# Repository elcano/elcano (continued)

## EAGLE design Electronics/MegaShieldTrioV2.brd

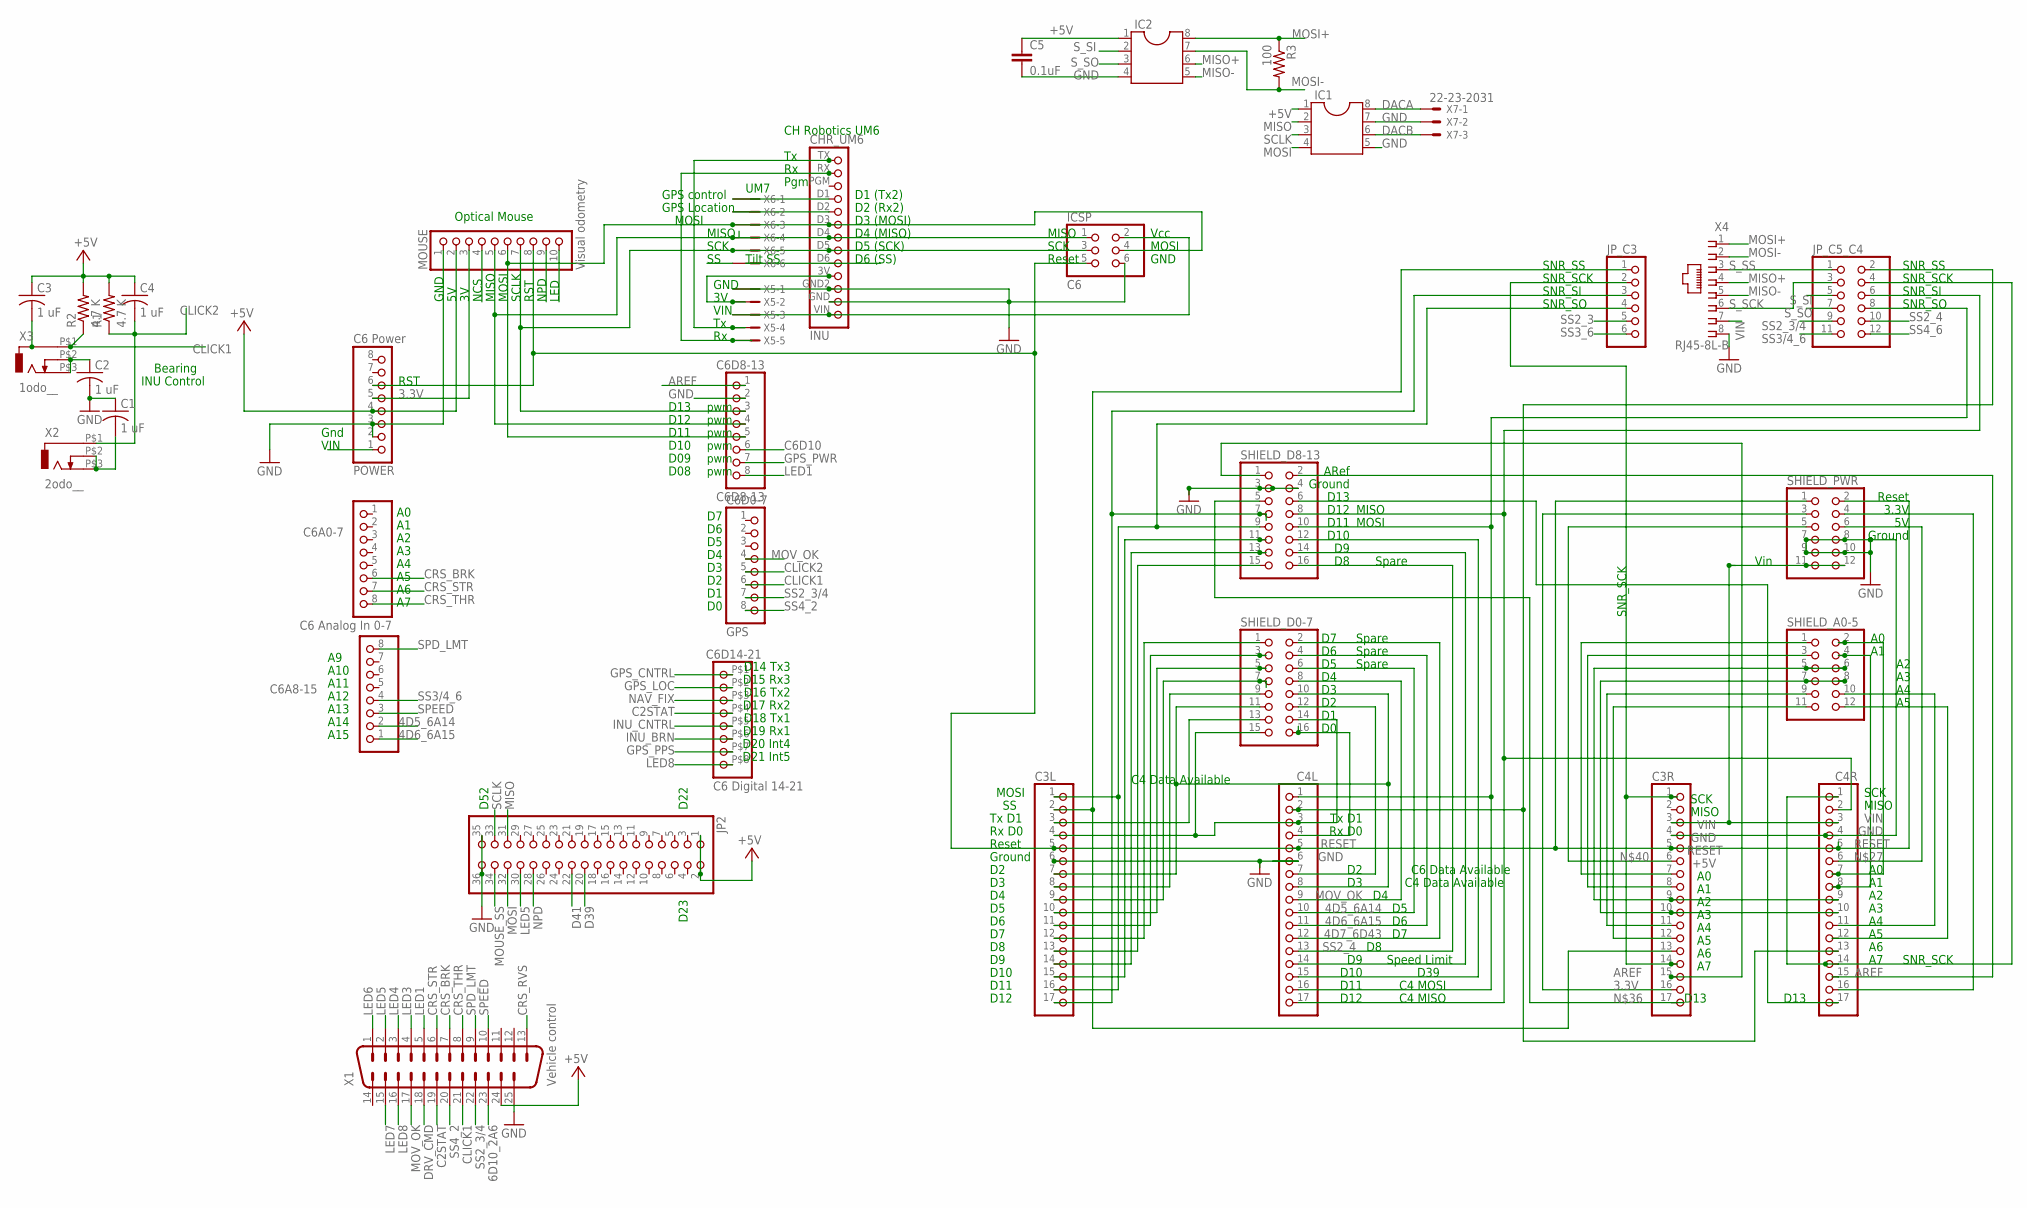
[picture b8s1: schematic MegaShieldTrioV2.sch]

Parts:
C1, C2, C3, C4: 1 uF; C025-030X050
C3L, C3R, C4L, C4R: PINHD-1X17; 1X17
C5: 0.1uF; C2.5-2
C6A0-7: C6 Analog In 0-7; 1X08
C6A8-15: 1X08
C6D0-7: GPS; 1X08
C6D8-13: C6D8-13; 1X08
C6D14-21: C6 Digital 14-21; 1X8HEADER
IC1, IC2: DIL8; DIL08
ICSP: C6; 2X03
INU: CHR_UM6
JP2: PINHD-2X18; 2X18
JP_C3: PINHD-1X6; 1X06
JP_C5_C4: PINHD-2X6; 2X06
MOUSE: Visual odometry; 1X10
POWER: C6 Power; 1X08
R1, R2: 4.7 K; 0207/10
R3: 100; 0204/5
SHIELD_A0-5: PINHD-2X6; 2X06
SHIELD_D0-7, SHIELD_D8-13: PINHD-2X8; 2X08
SHIELD_PWR: PINHD-2X6; 2X06
X1: Vehicle control; M25H
X2: 2odo__; ODO_JACK
X3: 1odo__; ODO_JACK
X4: RJ45-8L-B; RJ45-NO-SHIELD
X5: S5B-ZR
X6: S6B-ZR
X7: 22-23-2031

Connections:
3.3V: C3R.16, MOUSE.3, POWER.5, SHIELD_PWR.3
4D5_6A14: C4L.10, C6A8-15.2, SHIELD_D0-7.6
4D6_6A15: C4L.11, C6A8-15.1, SHIELD_D0-7.4
4D7_6D43: C4L.12, SHIELD_D0-7.2
6D10_2A6: X1.23
+5V: C3.1, C4.1, C5.1, IC1.1, IC2.1, JP2.1, JP2.2, MOUSE.2, POWER.4, R1.2, R2.2, X1.24
AREF: C3R.15, C4R.15, C6D8-13.1, SHIELD_D8-13.1, SHIELD_D8-13.2
C2STAT: C6D14-21.P$4 (4), X1.19
C4AVL: C3L.7, C4L.8, SHIELD_D0-7.10, SHIELD_D0-7.11
C4D12: C4L.17, C4R.2, SHIELD_D8-13.8
C6AVL: C4L.7, SHIELD_D0-7.12
C6D10: C6D8-13.6
CLICK1: C3.2, C6D0-7.6, R2.1, X1.21, X3.P$1 (1)
CLICK2: C4.2, C6D0-7.5, R1.1, X2.P$1 (1)
CRS_BRK: C3L.10, C6A0-7.6, SHIELD_D0-7.5, X1.7
CRS_RVS: X1.13
CRS_STR: C6A0-7.7, X1.6
CRS_THR: C6A0-7.8, X1.8
D39: JP2.20
D41: JP2.22
DACA: IC1.8, X7.1
DACB: IC1.6, X7.3
DRV_CMD: X1.18
F2RNG: C4R.12, SHIELD_A0-5.12
FL_RNG: C4R.8, SHIELD_A0-5.4
GND: C1.1, C2.2, C3L.6, C3R.4, C4L.6, C4R.4, C5.2, C6D8-13.2, IC1.5, IC1.7, IC2.4, ICSP.6, INU.GND (2), INU.GND2 (3), JP2.35, JP2.36, MOUSE.1, POWER.2, POWER.3, SHIELD_D8-13.3, SHIELD_D8-13.4, SHIELD_PWR.7, SHIELD_PWR.8, SHIELD_PWR.9, SHIELD_PWR.10, X1.25, X4.8, X5.1, X7.2
GPS_CNTRL: C6D14-21.P$1 (1), INU.D1 (10), X6.1
GPS_LOC: C6D14-21.P$2 (2)
GPS_PPS: C6D14-21.P$7 (7)
GPS_PWR: C6D8-13.7
INU_BRN: C6D14-21.P$6 (6)
INU_CNTRL: C6D14-21.P$5 (5)
INU_SS: INU.D6 (5)
LED1: C6D8-13.8, X1.5
LED3: X1.4
LED4: X1.3
LED5: JP2.30, MOUSE.10, X1.2
LED6: X1.1
LED7: X1.15
LED8: C6D14-21.P$8 (8), X1.16
L_RNG: C3R.10, C4R.10, SHIELD_A0-5.7, SHIELD_A0-5.8
MISO: C6D8-13.4, IC1.2, ICSP.1, INU.D4 (7), JP2.31, MOUSE.5, X6.4
MISO+: IC2.6, X4.4
MISO-: IC2.5, X4.5
MOSI: C6D8-13.5, IC1.4, ICSP.4, INU.D3 (8), JP2.32, MOUSE.6, X6.3
MOSI+: IC2.8, R3.1, X4.1
MOSI-: IC2.7, R3.2, X4.2
MOUSE_SS: JP2.34, MOUSE.4
MOV_OK: C4L.9, C6D0-7.4, SHIELD_D0-7.8, X1.17
unnamed: INU.3V (4), X5.2
unnamed: INU.D2 (9), X6.2
unnamed: INU.TX (13), X5.4
unnamed: C3R.7, SHIELD_A0-5.1
unnamed: C4R.7, SHIELD_A0-5.2
unnamed: C4R.16, SHIELD_PWR.4
unnamed: C2.1, X3.P$2 (2), X3.P$3 (3)
unnamed: INU.RX (12), X5.5
unnamed: C1.2, X2.P$2 (2), X2.P$3 (3)
unnamed: C4R.6, SHIELD_PWR.6
unnamed: C3R.17, SHIELD_D8-13.5
unnamed: C3L.3, SHIELD_D0-7.13
unnamed: ICSP.2, INU.VIN (1), X5.3
unnamed: C3R.6, SHIELD_PWR.5
unnamed: C3L.8, SHIELD_D0-7.9
unnamed: C3R.8, SHIELD_A0-5.3
unnamed: C3R.11, SHIELD_A0-5.9
unnamed: C3R.12, SHIELD_A0-5.11
unnamed: C3R.1, C3R.14, JP_C3.2
unnamed: C4R.1, C4R.14
unnamed: C4R.11, SHIELD_A0-5.10
unnamed: C4R.17, SHIELD_D8-13.6
unnamed: C3L.9, SHIELD_D0-7.7
unnamed: C3L.11, SHIELD_D0-7.3
unnamed: C3L.12, SHIELD_D0-7.1
unnamed: C3L.14, SHIELD_D8-13.13
unnamed: C3L.17, JP_C3.3, SHIELD_D8-13.7
unnamed: C3L.2, C3R.13, JP_C3.1
NAV_FIX: C4L.4, C6D14-21.P$3 (3), SHIELD_D0-7.16
NPD: JP2.28, MOUSE.9
PATH: C4L.3, SHIELD_D0-7.14, SHIELD_D0-7.15
RESET: C3L.5, C3R.5, C4L.5, C4R.5, ICSP.5, MOUSE.8, POWER.6, SHIELD_PWR.1, SHIELD_PWR.2
SCK: ICSP.3, INU.D5 (6), MOUSE.7, X6.5
SCLK: IC1.3, JP2.33
SNR_SEL: C4L.2, C4R.13, JP_C5_C4.2
SNR_SO: C4L.1, C4L.16, SHIELD_D8-13.10
SPD_LMT: C4L.14, C6A8-15.8, SHIELD_D8-13.14, X1.9
SPEED: C3L.1, C3L.16, C6A8-15.3, SHIELD_D8-13.9, X1.10
SS2_3: C3L.13, JP_C3.5, SHIELD_D8-13.15
SS2_3/4: C6D0-7.7, JP_C5_C4.9, X1.22
SS2_4: C4L.13, JP_C5_C4.10, SHIELD_D8-13.16
SS3/4_6: C6A8-15.4, JP_C5_C4.11
SS3_6: C3L.15, JP_C3.6, SHIELD_D8-13.11
SS4_2: C6D0-7.8, X1.20
SS4_6: C4L.15, JP_C5_C4.12, SHIELD_D8-13.12
S_SCK: JP_C5_C4.3, X4.6
S_SI: IC2.2, JP_C5_C4.5
S_SO: IC2.3, JP_C5_C4.7
S_SS: JP_C5_C4.1, X4.3
VIN: C3R.3, C3R.9, C4R.3, C4R.9, SHIELD_A0-5.5, SHIELD_A0-5.6, SHIELD_PWR.11, SHIELD_PWR.12, X4.7

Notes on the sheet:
pwm
Gnd
A10
A11
A13
A14
A15
D10
D11
D12
D13
D09
D08
VIN
Rx D0
Tx D1
Reset
Ground
3.3V
ARef
D14 Tx3
D15 Rx3
D16 Tx2
D17 Rx2
D18 Tx1
D19 Rx1
D20 Int4
D21 Int5
C4 Data Available
Speed Limit
INU Control
Bearing
Optical Mouse
GND
NCS
MISO
MOSI
SCLK
RST
NPD

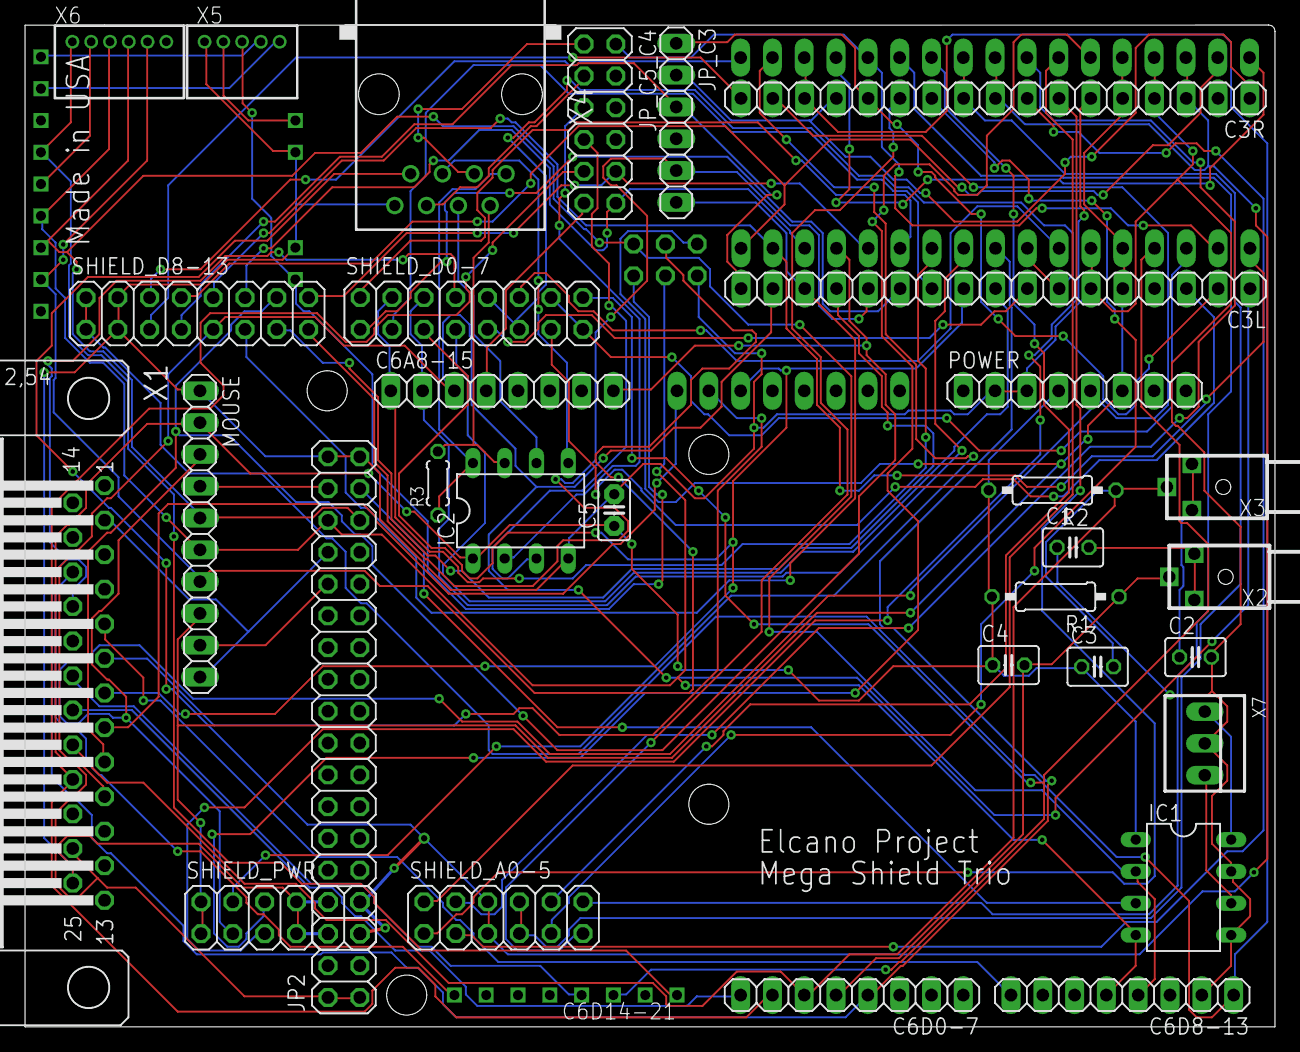
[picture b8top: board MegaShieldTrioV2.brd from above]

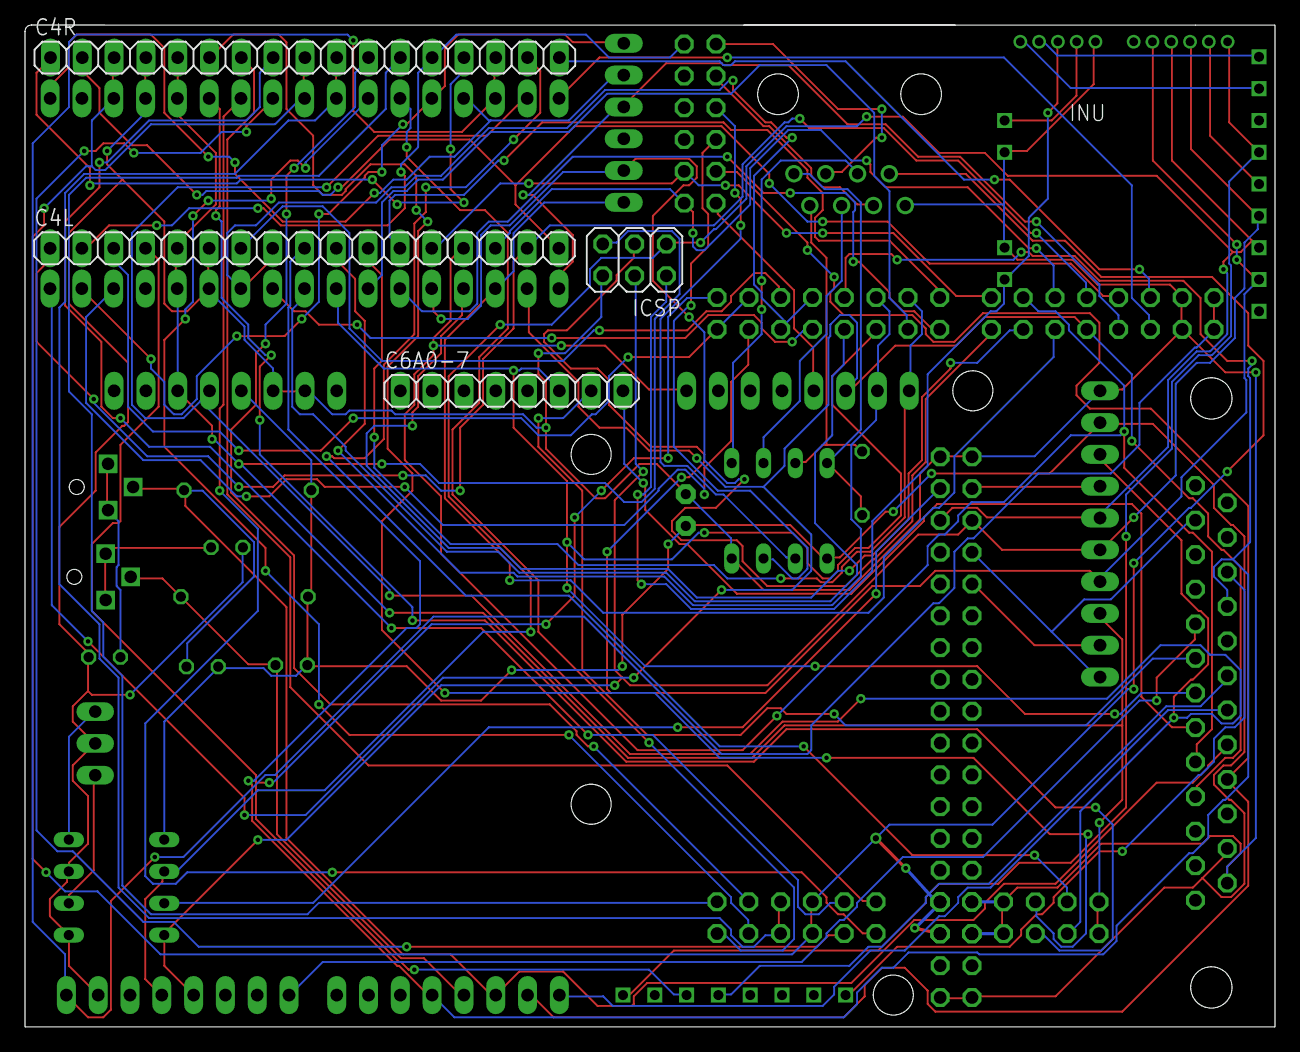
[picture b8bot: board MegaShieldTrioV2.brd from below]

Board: 2 copper layers, 99.8 x 80.0 mm, 37 parts (5 on the bottom side), 83 nets.

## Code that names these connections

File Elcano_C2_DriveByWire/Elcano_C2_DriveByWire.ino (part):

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  pinMode(CruiseLED, OUTPUT);
  pinMode(Throttle, OUTPUT);  // DEPRICATED: Use MOSI
  pinMode(DiskBrake, OUTPUT);
  pinMode(Steer, OUTPUT);
  pinMode(Reverse, OUTPUT);
  pinMode(ReverseLED, OUTPUT);
  pinMode(AccelerateJoystick, INPUT);
  pinMode(SteerJoystick, INPUT);
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  pinMode(Current36V, INPUT);
  pinMode(CurrentBrake, INPUT);
  pinMode(CurrentSteer, INPUT);
  pinMode(LED1, OUTPUT);
  pinMode(LED3, OUTPUT);
  pinMode(LED4, OUTPUT);
  pinMode(LED5, OUTPUT);
  pinMode(LED6, OUTPUT);
  pinMode(LED7, OUTPUT);
  pinMode(LED8, OUTPUT);
  Serial.begin(9600);
  initialize();
  attachInterrupt(0, CruiseRC1Pressed, RISING);
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
  Instrument[Motor].EnablePin = EnableThrottle;
  Instrument[Motor].SignalPin = Throttle;  // DEPRICATED: Use MOSI
  Instrument[Motor].FeedbackPin = 0; // Motor feedback is wheel speed
  Instrument[Motor].CurrentPin = Current36V;
  Instrument[Motor].StepSize = 20; // max from range of 1023.
  Instrument[Motor].CloseEnough = 1000;  // no feedback
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

  Instrument[Steering].EnablePin = EnableSteer;
  Instrument[Steering].SignalPin = Steer;
  Instrument[Steering].FeedbackPin = SteerFB;
  Instrument[Steering].CurrentPin = CurrentSteer;
  Instrument[Steering].StepSize = 20;
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
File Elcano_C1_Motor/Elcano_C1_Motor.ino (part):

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[in] Digital Signal 0: J1 pin 1 (RxD) Serial signal from C3 Pilot
  Serial input is a Gamebot command. Use of this syntax provides compatibility with the simulator.

  DRIVE {Speed ComandedSpinSpeed} {FrontSteer ComandedSteerAngle} 

  Where: 
  {Speed ComandedSpinSpeed} 	ComandedSpinSpeed is a ‘float’ giving the spin speed for the rear wheel. 
  The value is the absolute spin speed, in radians per second. 
  {FrontSteer ComandedSteerAngle} 	ComandedSteerAngle is a ‘float’ that specifies the steer angle 
  of Elcano’s front wheels. The value is the absolute steer angle, in radians. 
  
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  The signal is used to compute ActualSpinSpeed (radians/sec). */
const int Tachometer = 2;
 
/* [in] Digital Signal 3: J1 pin 4  (INT1) Halt or reset signal from console. 
*/
const int HaltCmd = 3;

/* [out] Digital Signal 4: J1 pin 5  (D4) Traction motor forward / reverse. */
const int Reverse = 4;

/* [out] Digital Signal 5: J1 pin 6  (D5) Actuator A1. Traction motor throttle. */
const int Throttle = 11;// 5;
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*/
const int SelectPID = 7;

const int Ack = 7;  // OBSOLETE: Acknowledge to C3 of reset request.

/* [out] Digital Signal 8: J3 pin 1 (D8) Enable Recombinant braking. 
  Alternatively, this could be hard-wired ON */
const int EnableRecombinant = 8;

/* [out] Digital Signal 9: J3 pin 2 (D9) PWM. Actuator A2: Brake Motor. 
  Controls disk brakes on left and right front wheels. Brakes are mechanically linked to operate in tandem. */
const int DiskBrake = 11; //9;

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
/* [out] Digital Signal 11: J3 pin 4 (D11) PWM. Actuator A3: Steering Motor. 
  Turns left or right. If no signal, wheels are locked to a straight ahead position. */
const int Steer = 5; // 11;

/* [out] Digital Signal 12: J3 pin 5 (D12) Enable Drive Motor. 
  Alternatively, this could be hard-wired ON */
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        pinMode(TxD, OUTPUT);
        pinMode(Tachometer, INPUT);
        pinMode(HaltCmd, INPUT);
        pinMode(Reverse, OUTPUT);
        pinMode(Throttle, OUTPUT);
        pinMode(SelectPID, OUTPUT);
        pinMode(EnableRecombinant, OUTPUT);
        pinMode(DiskBrake, OUTPUT);
        pinMode(Recombinant, OUTPUT);
        pinMode(Steer, OUTPUT);
        pinMode(EnableThrottle, OUTPUT);
        pinMode(LED, OUTPUT); 
//      analogReference(EXTERNAL);
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        
        motor.previous_error = 0;
        motor.integral = 0;
        steer.previous_error = 0;
        steer.integral = 0;
        motor.Kp = 0;
        digitalWrite( SelectPID, LOW);
        digitalWrite( EnableRecombinant, HIGH);
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 // TimeOfCmd is set to 0 and the other arguments read.
   GetSerial( &TimeOfCmd_ms, &CommandedSpinSpeed, &CommandedSteerAngle);
 
  // TO DO: Use differences in commanded and actual spin speed to control Drive, DiskBrake and Recombinant.
   ControlSpin(CommandedSpinSpeed);
 
 // TO DO: Read CurrentSteerAngle from SteerFeedback.
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
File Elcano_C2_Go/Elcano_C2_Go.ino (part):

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
// Joystick limits
const int limitStickUp = 893;  // observed
const int limitStickDown = 100;  // observed 0; but make everything from 0 to 100 full brake.
const int limitStickLeft = 900;  // guess
const int limitStickRight = 100; // guess

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{

  Instrument[Motor].SignalPin = Throttle;  // DEPRICATED: Use MOSI
  Instrument[Motor].FeedbackPin = 0; // Motor feedback is wheel speed
  Instrument[Motor].CurrentPin = Current36V;
  Instrument[Motor].StepSize = 20; // max from range of 1023.
  Instrument[Motor].CloseEnough = 100;  
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  Instrument[Motor].MinPosition = MinimumThrottle;  // position is 0-255
  Instrument[Motor].MaxPosition = FullThrottle;

  Instrument[Steering].SignalPin = Steer;
  Instrument[Steering].FeedbackPin = SteerFB;
  Instrument[Steering].CurrentPin = CurrentSteer;
  Instrument[Steering].StepSize = 20;
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  Serial.begin(9600);
  
  // SPI: set the slaveSelectPin as an output:
  pinMode (SelectAB, OUTPUT);
  pinMode (SelectCD, OUTPUT);
  pinMode (10, OUTPUT);
  SPI.setDataMode( SPI_MODE0);
  SPI.setBitOrder( MSBFIRST);
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
        pinMode(Throttle, OUTPUT);
        pinMode(DiskBrake, OUTPUT);
        pinMode(Steer, OUTPUT);
        pinMode(AccelerateJoystick, INPUT);
        pinMode(SteerJoystick, INPUT);
        pinMode(JoystickCenter, INPUT);
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
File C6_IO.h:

// I/O pins for C6 Navigator on Arduino Mega

// Analog inputs
#define C2_MOTOR_COMMANDED 8
#define C2_STEER_COMMANDED 9
#define C2_BRAKE_COMMANDED 10

// Digital
// D0 is serial monitor in
#define Rx0  0
// D1 is serial monitor out
#define Tx0  1

// pulse from GPS once per second; used to sysnc to GPS time
// Define as 2 if use interrupt
// If no interrupt is needed, defining as 7 allows using a jumper connector
#define GPS_PPS 2
// click once per wheel revolution
// This signal can be pin 3 on a base Arduino.
// When using a Mega, pin 21 offers easier wiring.
#define CYCLOMETER 21
#define GPS_POWER  4
#define GPS_GREEN_LED 5
#define GPS_RED_LED 6
#define SPEED_PIN  9
// D10 to D13 are for SD card on shield
const int chipSelect = 10;  // for SD data logging shield from Adafruit.
/** MOSI - pin 11
 ** MISO - pin 12
 ** CLK  - pin 13 */
const int LED = 13;

// Serial 3
#define GPS_RX  14
#define GPS_TX  15
// Serial 2 for intended state and estimated state
#define C4_TX   16
#define C4_RX   17
// Serial 1 for digital compass and inertial measurement unit
#define INU_TX  18
#define INU_RX  19
// pin 21 is CYCLOMETER

// Analog inputs
const int Front = 0;
const int Right = 1;
const int Left = 2;

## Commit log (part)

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2018-06-14 New PCB for HighLevel and LowLevel; Low level is not quite as built; needs to be updated
2018-06-25 Adding unified transmitter-receiver code. Receiver code interfaces with C2 using ElcanoSerial.
2018-08-15 s/angle_deg/angle_mDeg/g ; and whitespaces
2018-08-15 update ElcanoSerial
2018-08-17 resynch other files with master branch.
2018-08-23 Adding support for Spektrum ESTOP signal; the Spektrum receiver is not currently working so this has not yet been tested live.
2018-08-26 removing extra nested RC folder
2018-08-26 This change adds the number field to a drive packet, otherwise this is ommitted from the packet even if the field is set.
2018-08-26 I fixed the loop timing by taking out the subtraction that underflowed the delay time. The new statements also pass through (no delay) if we have a loop longer than LOOP_TIME_MS. Previously, we were 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
2018-09-04 Created DEBUG value, Moved output to a conditional block
    We do not normally use the serial output and it slows execution time. I increased the baud rate (making it the same as ElcanoSerial)
2018-09-04 Adding functions to convert byte values to throttle and turn using linear functions
2018-09-04 Adding RC angle and throttle conversion funcitons to main loop
2018-09-06 Debug output tweaks, added loop start time and changed formatting
2018-09-06 Using float variables (to avoid integer division) to "map" RC turn values to us pulses
    Also moved throttle and turn trim operations ot the transmitter code
2018-09-13 debugging output on brakes, RC now bypasses steering and brake PIDs (the user is the PID), using a float to convert byte steering value to microseconds if throttle is neagative and we're using RC (by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
2018-10-26 C2-LL changes: - Added a "DEBUG" variable and put most serial monitor output statements in a debugging conditional. - changed include statements; elcanoserial.h and settings.h are not default directo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
2018-11-16 The loop timing code is buggy. It uses an unsigned variable for a signed quantity that is almost certainly negative. Observed symptom was that the loop went through one pass then hung. That is consis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
2018-12-07 Added a debugging conditional. Added debugging messages in place of unconditional serial printouts. Integrated functions to convert RC values to LL values
2018-12-07 changed quotes to angle brackets in C2 includes
2018-12-07 Do floating point division in conversion from byte turn values to servo us.
2018-12-23 Adding SCH and BRD files for RC Transmitter unit. This board is designed for an arduino micro, two joysticks, indicator LEDs, (power, estop, and auto) switches, and a 3-pin ASK radio.
2019-01-19 Deleted obsolete documentation
    File from 2011 are no longer relevant.
2019-03-13 Ignore .s# Eagle CAD backup files
2019-03-13 Deleted old documentation
2019-03-13 Moved old electronics to archive
2019-03-20 Function printTx modified to form entire string before printing anything
2019-03-27 Current
2019-03-27 noted differences between current code and JBreithaupts
2019-03-27 Commented out header files
    I would like to be able to test on the trike before fully deleting code
2019-03-27 Removed/ Added to correct folder
2019-03-27 Changed pin number for relays
2019-03-27 update MoveActuator by using Serial.h
    Added servo library, formatting changes
2019-03-27 Move the Brakes class out
2019-03-27 electronics update!
    moved a lot of stuff to get the board smaller, added ground planes, added CANbus 3-pin header, fixed all the silkscreening
2019-03-27 added PWM output on steering header and 120ohm terminating resistor for CAN
    forgot to commit this...
2019-03-27 added Eagle temp file types to gitignore
2019-03-27 removed accidental debugging Mega, added a handful of vias to fix GND orphans
2019-03-27 schematic cleanup
2019-03-27 organized into class structures
2019-03-27 Forgot to save
2019-03-27 minor changes to vehicle and lowlevel
    next step fix interpolation
2019-03-27 fixed silkscreen in old v2
2019-03-27 Added reset button to top of board
2019-03-27 moveactuator updated to work with known values for Servo.h and the yellow trike
2019-03-27 started updateSpeed in ThrottleController
2019-03-27 finished refactor
2019-03-27 removed files from top level files
2019-03-27 removed old version
2019-03-27 Bugs fixed
2019-03-27 added figure8 script
2019-03-27 Added three simple function-test sketches
2019-03-27 eagle project file meta update
2019-03-27 moved demo test into a folder
    also removed the PID library meta files because they're embarassing
2019-03-27 changed serial.prints, added beginTransaction and endTransaction for SPI
2019-03-27 Fixed dac error
2019-03-27 fixed spelling
2019-03-27 fixed spelling error in folder name
2019-03-27 Many LLBv3 updates in one!
    re-arranged inerrupt pins to share a PCI ISR, added RC circuit to MCP2515 per datasheet, replaced impossible capacitor, re-arranged oscilator layout
2019-03-27 fixed bad late night code
2019-03-27 Added e-stop, routed additional connetions to DB15, changed board layout
2019-03-27 LLBv3 routing overhaul
    applied restriction polygons and added many vias to prevent GND airwires
2019-03-27 added dimensions to board
2019-03-27 partial routing, adding restrict polys
2019-03-27 re-routed watchdog from digi-5 to DB15 thru middle instead of along edge
2019-03-27 added .pro to git ignore
2019-03-27 updated LLBv3 pin mapping document; matches current state of board
2019-03-27 Updates to board, schematic, library
    added 4.7k pullup to odometer and took first steps towards replacing the arduino headers with custom component with correct pin names.
2019-03-27 corrected PCINT pin mapping
    moved pretty much every interrupt pin to A8-A15, which had the secondary benefit of greatly reducing their trace length.
2019-03-27 board cleanup, via removal, silkscreen tidying
    * Changing size of almost every 'tvalue' item
    * slightly tweaked trace location to allow for greater ground plane coverage
    * removed redundant ground vias
    * began renaming devices for clarity
2019-03-27 added hardware parts designed last quarter
2019-03-27 lots of renaming and slight position changes
    * renamed caps and resistors to make populating the board a little easier
    * moved silk around to try and be a little more coherent
    * slight copper adjustments to get more ground fill
2019-03-27 updated based on demo code
2019-03-27 fixed ino code
2019-03-27 Made recommended changes
    Notes on Low Level Code
    Good organization with Vehicle, Brake, ThrottleController etc. classes.
    The only thing in the main loop is vehicle.update, which checks the brakes, computes the speed and the steering angle. It does not set the throttle, so there is no way to make the trike go. It does n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
    I added the existing communication code from the elcano/elcano repo but this is the section we will be reworking for can
    There are two reasons to avoid doubles. I would prefer to see doubles eliminated from the code, exce
2019-03-27 added screw terminal to BoM
2019-03-27 Checkpoint for first PCB order
    * few minor routing changes
    * extended a 1x8 to a 1x10 because some Mega boards have two more pins on one header.
    * added partial bill of materials
2019-03-27 Added URL for click-jack to BoM
2019-03-27 interrupts contained in appropriate class
2019-03-27 first foray into sorting the electronics folder and filtering out obselete designs
    Do note that files in folders may not have access to the ElcanoParts library
2019-03-27 expanded copper for relay module, moved drills for odometer away from board edge
2019-03-27 Initial commit of LLBv3 function tests
2019-03-27 LLBv3 corrections
    Fixed silk-via overlapping regions.
    Fixed reset button schematic/wiring, now connects reset to ground.
    Swapped CAN differential pair pinout by fixing the part in the library and re-routing the board.
    Moved some surface mount parts to better propagate the ground plane.
    Added on-silkscreen documentation for CAN and relay pinouts.
    Added power-OK led and its resistor.
2019-03-27 also corrected pinout definition
2019-03-27 Created initial version of a 'settings.h' file for the LLBv3.
2019-03-27 add CAN bus command
2019-03-27 Added RJ45 modular jack to Elcanoparts library
2019-03-27 Corrections to silkscreen, added testpoints
    Fixed silkscreen errors around the relay terminals, added symbols.
    Added testpoints and easily cut traces for steering header ground pins, for future expandability options.
2019-03-27 Removed DACB from the DB15 connector. Pin 13 will now be used by the manual throttle as a 5V source.
    Also added a pair of test points for DAC channels A & B.
2019-03-27 LLBv3.1 changes
    Rerouted high-current relay circuit to handle swapped NC/NO pins.
    Replaced 10-pin connector with 8-pin RJ45 modular jack. Expensive mistake.
    Added debug LED on pin D13.
    Added test points for steering header.
    Silkscreen and routing corrections.
2019-03-27 Added document to describe the steering header pin mapping on a CAT5E
2019-03-27 Minor update to high current traces to increase surface area
2019-03-27 Low level with CAN receive
2019-03-27 Update CAN message command
2019-03-27 Rename lowLevel.ino to Elcano_C2_LowLevel/lowLevel.ino
2019-03-27 removed extra lowlevel code
2019-03-27 moved llbv3 settings
2019-03-27 added can messaging
2019-03-27 Added tests for LLBv3.1, now capable of testing the cyclometer
    Demo code for using PCINT, too.
    Functionally the same, but major refactor work
2019-03-27 Defined odo click for function test
2019-03-27 Minorsilkscreen updates
    Named testpoints
    Swapped 10k for 0 ohm resistor on reset button
2019-03-27 integrated CAN
2019-03-27 added some interrupt handlers, simplified classes
2019-03-27 Coerced firmware to compile
    receiveCAN() cannot be a static method
    attempted to move interrupts to constructor, but I don't have the energy to fight the static-member fight
2019-03-27 Updated llbv3 bill of materials
2019-03-27 Cleanup
    * remove two extraineous files from the PID library that was copied in
    * remove over-specification on the update() method of the vehicle class
2019-03-27 bug fix
    wrong argument in map
2019-03-27 started working on angle translation, partially written function is never called and is work in progress with many comments
2019-03-27 investigating bugs
2019-03-27 fixing bugs
2019-03-27 added steer tester
2019-03-27 Corrected pin mapping document for steering PWM pin
2019-03-27 Removed extra
2019-03-27 fixed steering
2019-03-27 Add CAN and high level test
2019-03-27 Add more high level comments and tests
2019-03-27 added vs files to gitignore
2019-04-01 High level code from Self-Drive repo
2019-04-23 Create High_Level_System.ino
    Copied from Self-Drive with lots of DEBUG comments to be removed later
2019-04-23 New CAN test files
    Low is changed by Hilevel and verified by msgs sent back from Low.
2019-05-01 Updated Serial to CAN
2019-05-07 Switched of PIDs again, all mmPs now
2019-05-07 Working Throttle with delay?
2019-05-08 removed all delays > 1ms
2019-05-15 First go at modulizing code
2019-05-15 updated for testing
2019-05-15 Added Test Directory to keep real code intact
2019-05-16 Finished Seperating all Classes for High Level
2019-05-17 Changes for highlevel
2019-05-18 origin and estimated_pos passed through to Nav and Planner
2019-05-27 initialize and map select good. Now work on plan
2019-05-28 Made some distinctions in System and Test
2019-05-29 fixed distance
2019-05-31 added haversine variable moved common variables to settings
2019-06-06 gyroscope added. now check why not initialize
2019-06-06 Redoing the code with kims
2019-06-10 Folsom Folder Choice
2019-06-10 SolidWorks files for Brake System for ELF
2019-06-10 LIDAR SolidWorks files
2019-06-13 Added ObstacleAvoidance.h
2019-06-13 Consolidated with Kims
2019-06-13 Fixed directories by Folsom's specs
2019-06-13 BUgs in sending proper turn angle
    in proper_heading method in TEST, in PILOT returning incorrect angle to low level baord bugs
